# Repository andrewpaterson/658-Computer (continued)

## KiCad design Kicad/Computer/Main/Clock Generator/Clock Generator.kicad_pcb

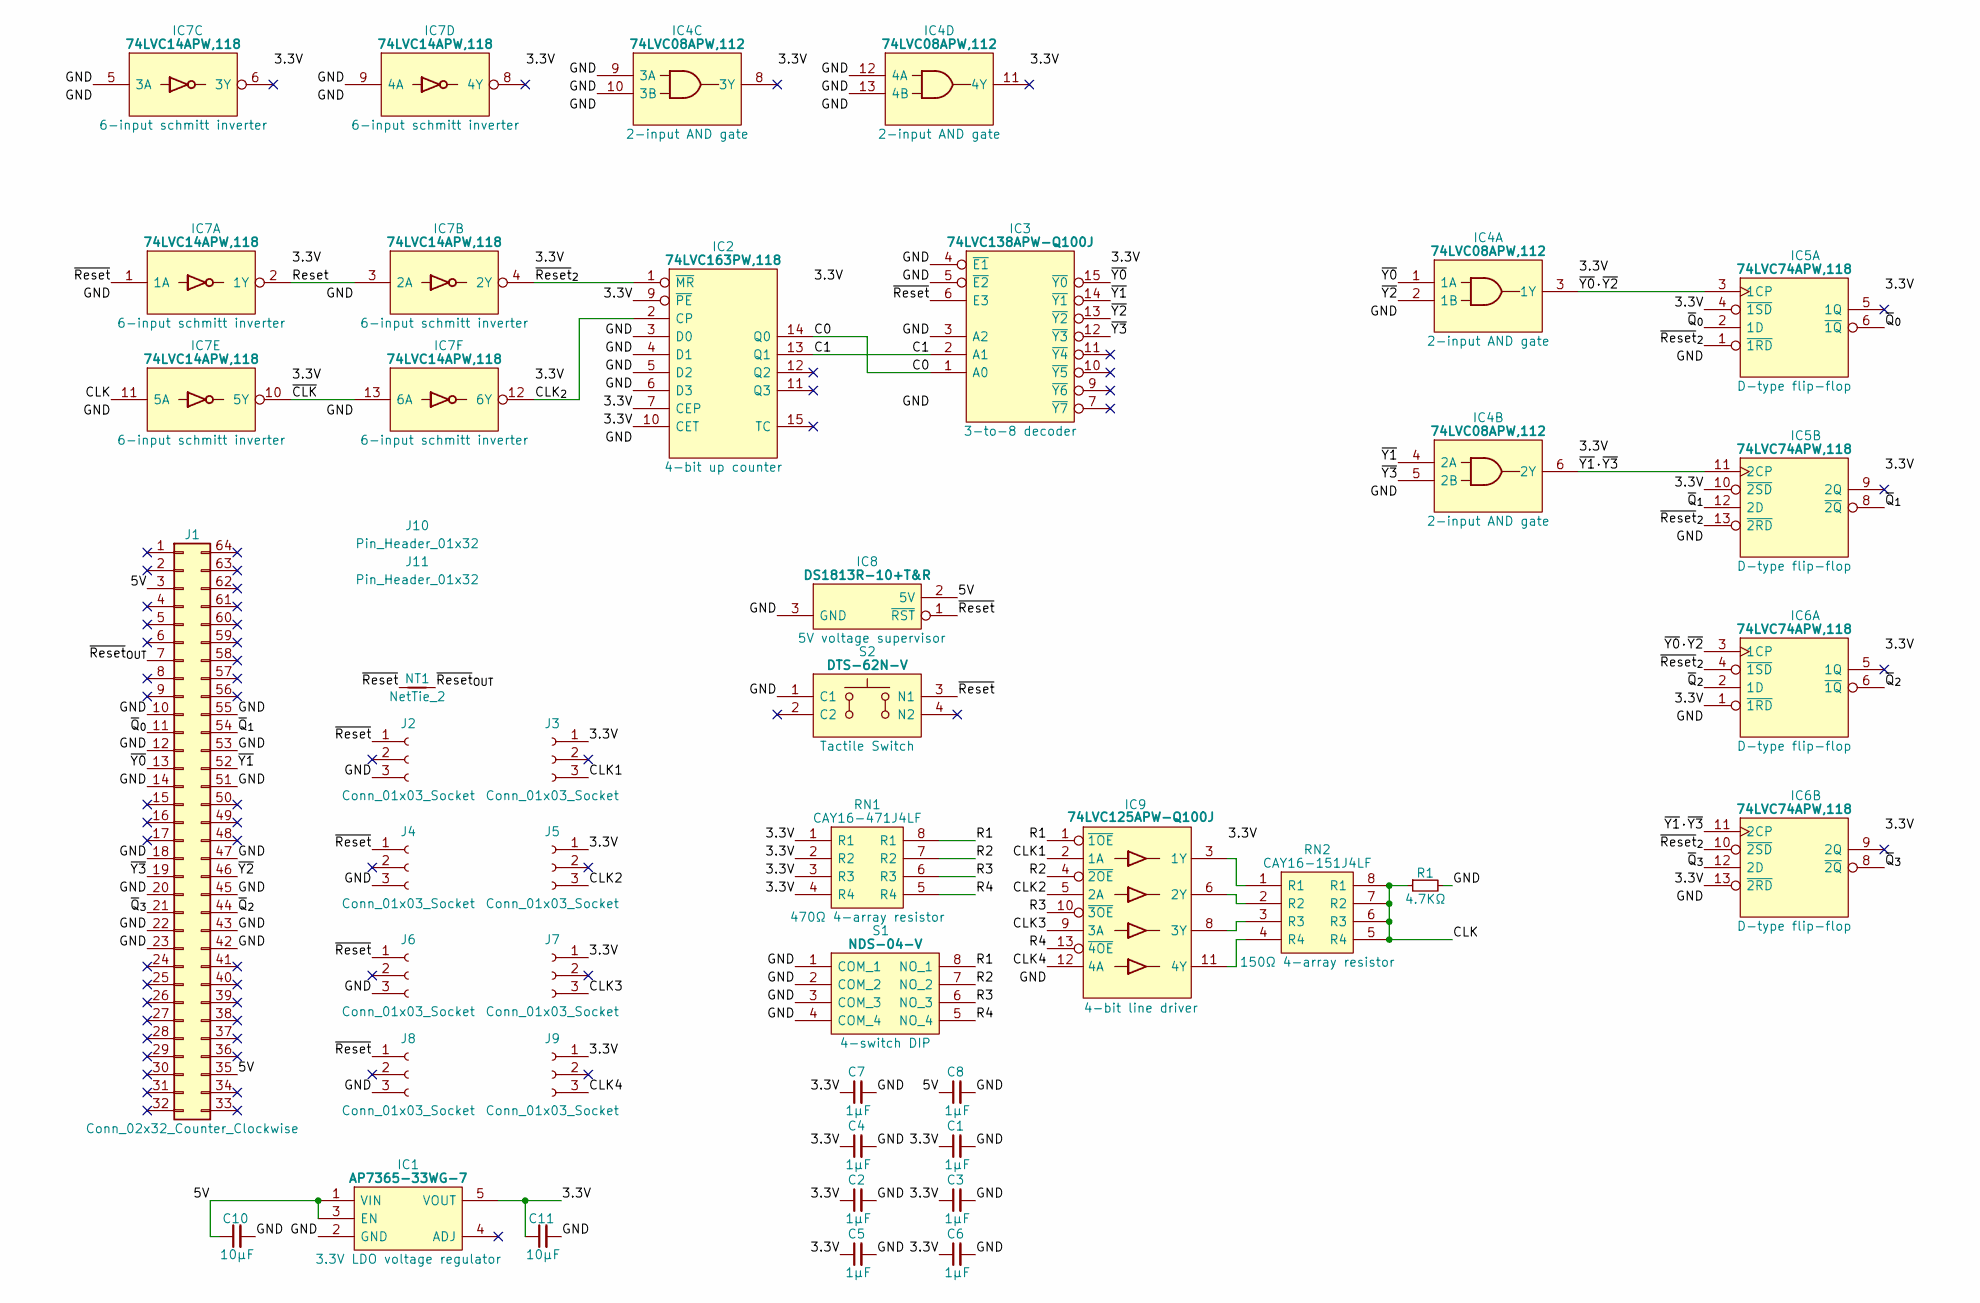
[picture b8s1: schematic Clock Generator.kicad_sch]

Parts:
C1, C2, C3, C4, C5, C6, C7, C8: 1μF; C_0805
C10, C11: 10µF; C_0805
IC1: AP7365-33WG-7; SOT95P285X130-5N; Manufacturer_Part_Number AP7365-33WG-7; Mouser Part Number 621-AP7365-33WG-7
IC2: 74LVC163PW,118; SOP65P640X110-16N; Mouser Part Number 771-74LVC163PW-T
IC3: 74LVC138APW-Q100J; SOP65P640X110-16N; Mouser Part Number 771-74LVC138APWQ100J
IC4: 74LVC08APW,112; SOP65P640X110-14N; Manufacturer_Part_Number 74LVC08APW,112; Mouser Part Number 771-74LVC08APW
IC5, IC6: 74LVC74APW,118; SOP65P640X110-14N; Mouser Part Number 771-74LVC74APW-T
IC7: 74LVC14APW,118; SOP65P640X110-14N; Manufacturer_Part_Number 74LVC14APW,118; Mouser Part Number 771-74LVC14APW-T
IC8: DS1813R-10+T&R; SOT95P237X112-3N; Mouser Part Number 700-DS1813R-10T&R
IC9: 74LVC125APW-Q100J; SOP65P640X110-14N; Manufacturer_Part_Number 74LVC125APW-Q100J; Mouser Part Number 771-74LVC125APWQ100J
J1: Conn_02x32_Counter_Clockwise; DIP-64_Board_W22.86mm
J2, J3, J4, J5, J6, J7, J8, J9: Conn_01x03_Socket; PinSocket_1x03_P2.54mm_Vertical
J10, J11: Pin_Header_01x32; PinHeader_1x32_P2.54mm_Vertical
NT1: NetTie_2; NetTie-2_SMD_Pad0.5mm
R1: 4.7KΩ; R_0805
RN1: CAY16-471J4LF; CAY16-J4; Manufacturer_Part_Number CAY16-471J4LF; Mouser Part Number 652-CAY16-471J4LF
RN2: CAY16-151J4LF; CAY16-J4; Manufacturer_Part_Number CAY16-151J4LF; Mouser Part Number 652-CAY16-151J4LF
S1: NDS-04-V; NDS04V; Manufacturer_Part_Number NDS-04-V; Mouser Part Number 642-DS04
S2: DTS-62N-V; DTS62NV; Manufacturer_Part_Number DTS-62N-V; Mouser Part Number 113-DTS-62N-V

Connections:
/3.3V: C1.1, C2.1, C3.1, C4.1, C5.1, C6.1, C7.1, C11.1, IC1.5 (VOUT), IC2.7 (CEP), IC2.9 (~PE), IC2.10 (CET), IC2.16 (3V), IC3.16 (3V), IC4.14 (3V), IC5.4 (~1SD), IC5.10 (~2SD), IC5.14 (3V), IC6.1 (~1RD), IC6.13 (~2RD), IC6.14 (3V), IC7.14 (3V), IC9.14 (3V), J3.1, J5.1, J7.1, J9.1, RN1.1 (R1), RN1.2 (R2), RN1.3 (R3), RN1.4 (R4)
/5V: C8.1, C10.1, IC1.1 (VIN), IC1.3 (EN), IC8.2 (5V), J1.3, J1.35
/C0: IC2.14 (Q0), IC3.1 (A0)
/C1: IC2.13 (Q1), IC3.2 (A1)
/CLK: IC7.11 (5A), R1.1, RN2.5 (R4), RN2.6 (R3), RN2.7 (R2), RN2.8 (R1)
/CLK1: IC9.2 (1A), J3.3
/CLK2: IC9.5 (2A), J5.3
/CLK3: IC9.9 (3A), J7.3
/CLK4: IC9.12 (4A), J9.3
/CLK_{2}: IC2.2 (CP), IC7.12 (6Y)
/GND: C1.2, C2.2, C3.2, C4.2, C5.2, C6.2, C7.2, C8.2, C10.2, C11.2, IC1.2 (GND), IC2.3 (D0), IC2.4 (D1), IC2.5 (D2), IC2.6 (D3), IC2.8 (GND), IC3.3 (A2), IC3.4 (~E1), IC3.5 (~E2), IC3.8 (GND), IC4.7 (GND), IC4.9 (3A), IC4.10 (3B), IC4.12 (4A), IC4.13 (4B), IC5.7 (GND), IC6.7 (GND), IC7.5 (3A), IC7.7 (GND), IC7.9 (4A), IC8.3 (GND), IC9.7 (GND), J1.10, J1.12, J1.14, J1.18, J1.20, J1.22, J1.23, J1.42, J1.43, J1.45, J1.47, J1.51, J1.53, J1.55, J2.3, J4.3, J6.3, J8.3, R1.2, S1.1 (COM_1), S1.2 (COM_2), S1.3 (COM_3), S1.4 (COM_4), S2.1 (C1)
/R1: IC9.1 (~1OE), RN1.8 (R1), S1.8 (NO_1)
/R2: IC9.4 (~2OE), RN1.7 (R2), S1.7 (NO_2)
/R3: IC9.10 (~3OE), RN1.6 (R3), S1.6 (NO_3)
/R4: IC9.13 (~4OE), RN1.5 (R4), S1.5 (NO_4)
/Reset: IC7.2 (1Y), IC7.3 (2A)
/~CLK: IC7.10 (5Y), IC7.13 (6A)
/~Q_{0}: IC5.2 (1D), IC5.6 (~1Q), J1.11
/~Q_{1}: IC5.8 (~2Q), IC5.12 (2D), J1.54
/~Q_{2}: IC6.2 (1D), IC6.6 (~1Q), J1.44
/~Q_{3}: IC6.8 (~2Q), IC6.12 (2D), J1.21
/~Reset: IC3.6 (E3), IC7.1 (1A), IC8.1 (~RST), J2.1, J4.1, J6.1, J8.1, NT1.1, S2.3 (N1)
/~Reset_{2}: IC2.1 (~MR), IC5.1 (~1RD), IC5.13 (~2RD), IC6.4 (~1SD), IC6.10 (~2SD), IC7.4 (2Y)
/~Reset_{OUT}: J1.7, NT1.2
/~Y0: IC3.15 (~Y0), IC4.1 (1A), J1.13
/~Y0·~Y2: IC4.3 (1Y), IC5.3 (1CP), IC6.3 (1CP)
/~Y1: IC3.14 (~Y1), IC4.4 (2A), J1.52
/~Y1·~Y3: IC4.6 (2Y), IC5.11 (2CP), IC6.11 (2CP)
/~Y2: IC3.13 (~Y2), IC4.2 (1B), J1.46
/~Y3: IC3.12 (~Y3), IC4.5 (2B), J1.19
unnamed: IC9.3 (1Y), RN2.1 (R1)
unnamed: IC9.6 (2Y), RN2.2 (R2)
unnamed: IC9.8 (3Y), RN2.3 (R3)
unnamed: IC9.11 (4Y), RN2.4 (R4)

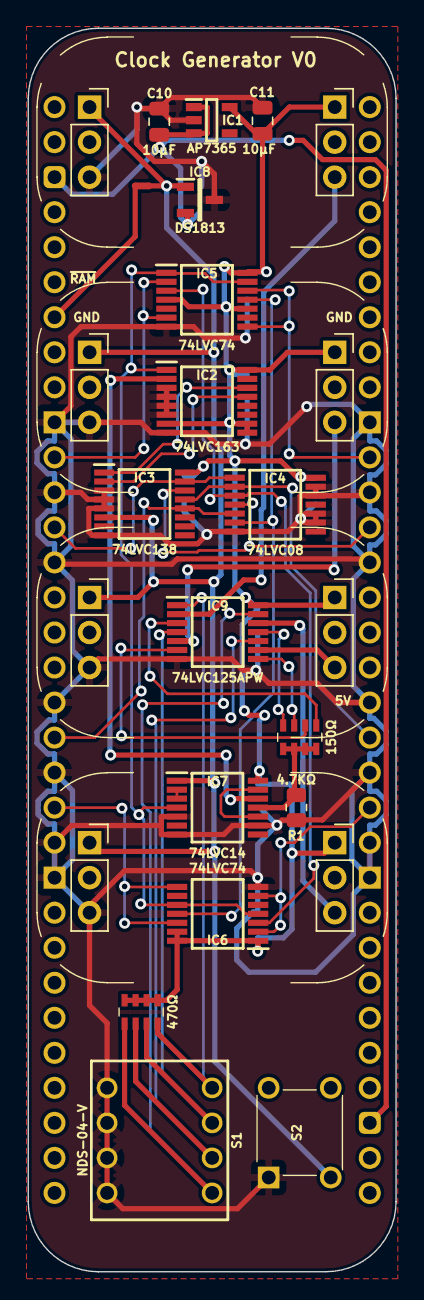
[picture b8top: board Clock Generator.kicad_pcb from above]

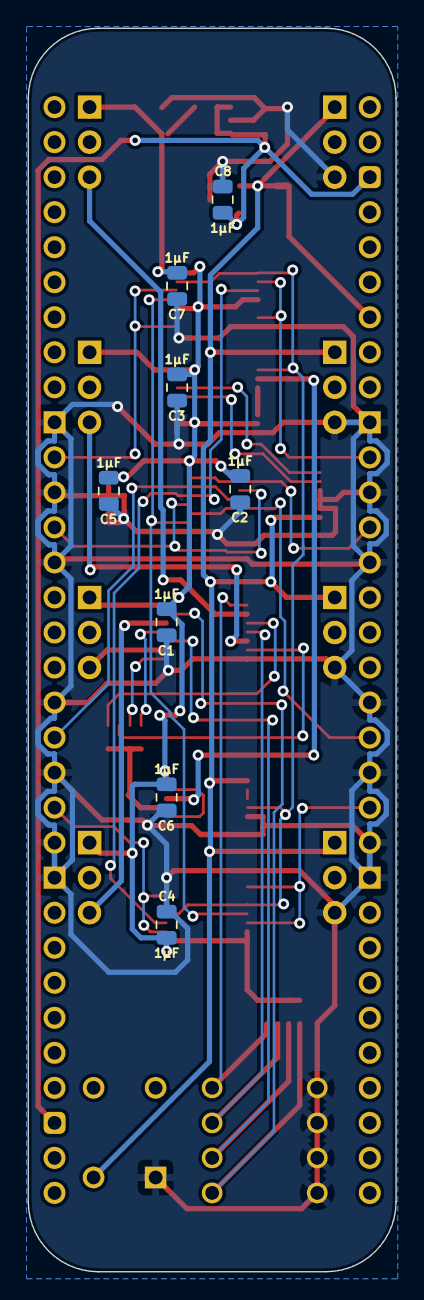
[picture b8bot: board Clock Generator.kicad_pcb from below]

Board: 2 copper layers, 26.7 x 90.2 mm, 36 parts (10 on the bottom side), 34 nets.
